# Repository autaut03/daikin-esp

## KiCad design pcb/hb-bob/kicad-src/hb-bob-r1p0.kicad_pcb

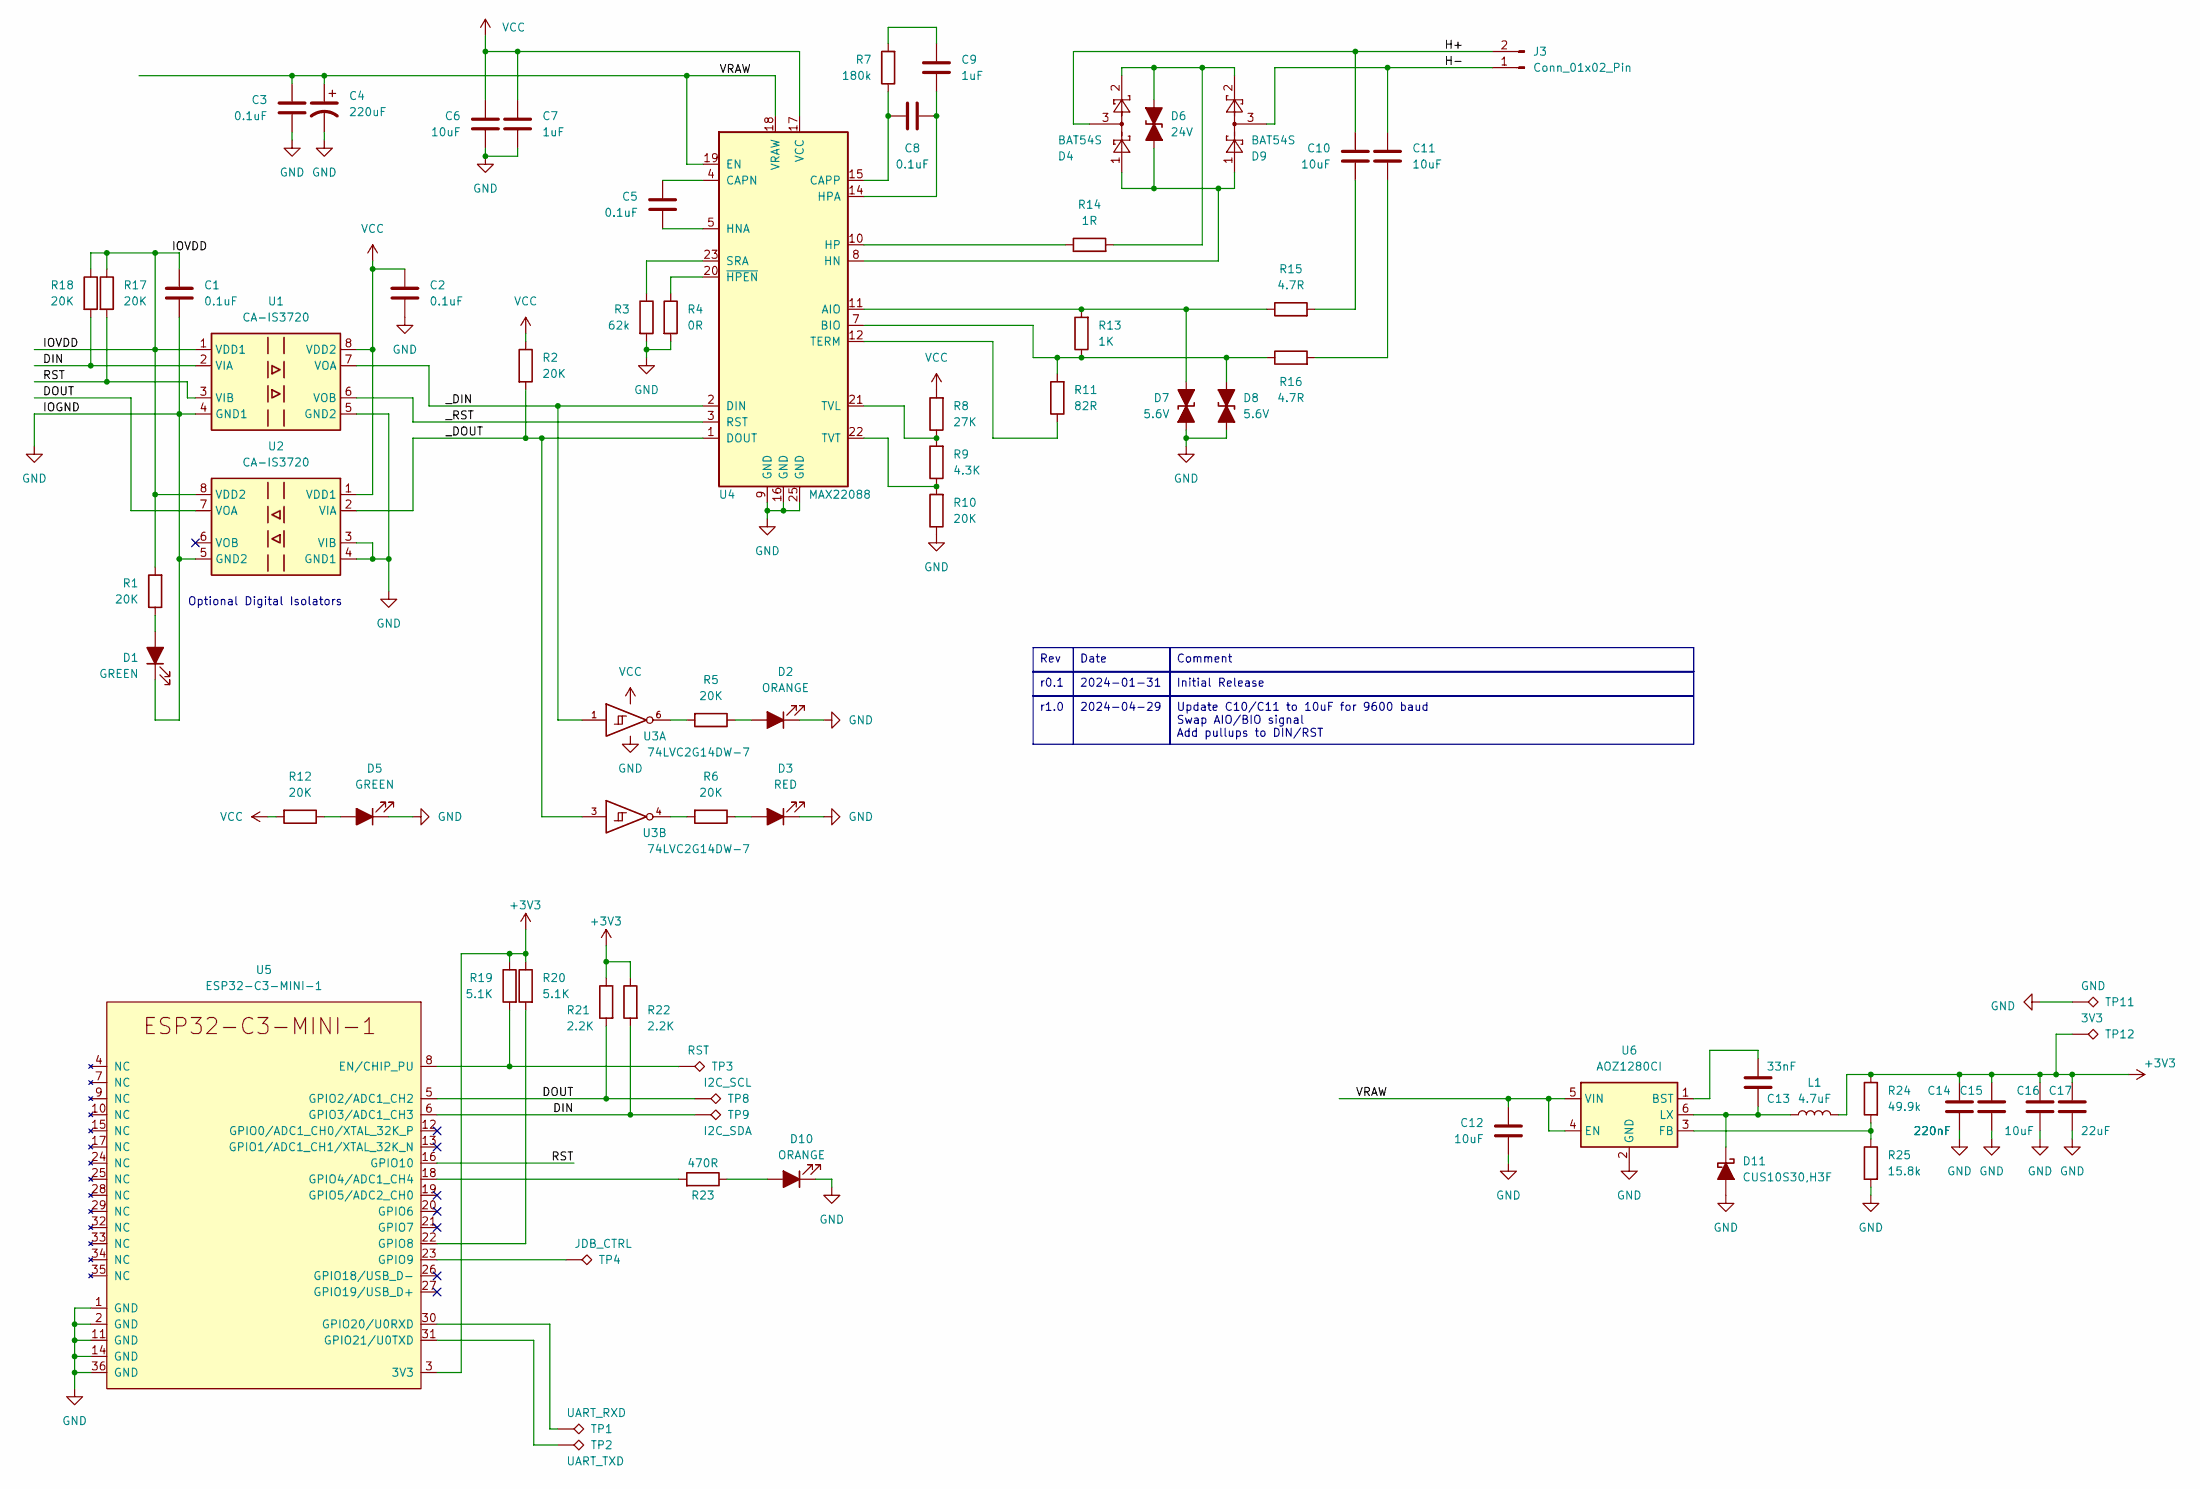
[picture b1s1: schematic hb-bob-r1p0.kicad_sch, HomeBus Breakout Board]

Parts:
C1, C2, C3, C5, C8: 0.1uF; C_0402_1005Metric; LCSC C1525
C4: 220uF; CP_EIA-7360-38_Kemet-E_Pad2.25x4.25mm_HandSolder; LCSC C2918361
C6, C10, C11: 10uF; C_0402_1005Metric; LCSC C15525
C7, C9: 1uF; C_0402_1005Metric; LCSC C52923
C12: 10uF; C_0603_1608Metric; LCSC C15850
C13: 33nF; C_0402_1005Metric; LCSC C106862
C14, C15: 220nF; C_0402_1005Metric; LCSC C16772
C16: 10uF; C_0603_1608Metric; LCSC C19702
C17: 22uF; C_0603_1608Metric; LCSC C59461
D1, D5: GREEN; LED_0402_1005Metric; LCSC C165980
D2: ORANGE; LED_0402_1005Metric; LCSC C165980
D3: RED; LED_0402_1005Metric; LCSC C165980
D4, D9: BAT54S; SOT-23; LCSC C916425
D6: 24V; D_SOD-123F; LCSC C908212
D7, D8: 5.6V; D_SOD-923; LCSC C151980
D10: ORANGE; LED_0402_1005Metric; LCSC C965791
D11: CUS10S30,H3F; D_SOD-523; LCSC C8523
J3: Conn_01x02_Pin; PinHeader_1x02_P2.54mm_Horizontal
L1: 4.7uF; L_0805_2012Metric; LCSC C63166
R1, R2, R5, R6, R10, R12, R17, R18: 20K; R_0402_1005Metric; LCSC C25765
R3: 62k; R_0402_1005Metric; LCSC C37825
R4: 0R; R_0402_1005Metric; LCSC C60485
R7: 180k; R_0402_1005Metric; LCSC C25760
R8: 27K; R_0402_1005Metric; LCSC C25771
R9: 4.3K; R_0402_1005Metric; LCSC C25899
R11: 82R; R_0402_1005Metric; LCSC C2909389
R13: 1K; R_0402_1005Metric; LCSC C11702
R14: 1R; R_0805_2012Metric; LCSC C131397
R15, R16: 4.7R; R_0603_1608Metric; LCSC C137705
R19, R20: 5.1K; R_0402_1005Metric; LCSC C25905
R21, R22: 2.2K; R_0402_1005Metric; LCSC C25879
R23: 470R; R_0402_1005Metric; LCSC C25117
R24: 49.9k; R_0402_1005Metric; LCSC C25897
R25: 15.8k; R_0402_1005Metric; LCSC C26956
TP1: UART_RXD; TestPoint_Pad_D1.0mm
TP2: UART_TXD; TestPoint_Pad_D1.0mm
TP3: RST; TestPoint_Pad_D1.0mm
TP4: JDB_CTRL; TestPoint_Pad_D1.0mm
TP8: I2C_SCL; TestPoint_Pad_D1.0mm
TP9: I2C_SDA; TestPoint_Pad_D1.0mm
TP11: GND; TestPoint_Pad_D1.0mm
TP12: 3V3; TestPoint_Pad_D1.0mm
U1, U2: CA-IS3720; SOIC-8_3.9x4.9mm_P1.27mm; LCSC C428882
U3: 74LVC2G14DW-7; SOT-363_SC-70-6; LCSC C362110
U4: MAX22088; QFN-24-1EP_4x4mm_P0.5mm_EP2.6x2.6mm; LCSC C5258925
U5: ESP32-C3-MINI-1; LCSC C2934569
U6: AOZ1280CI; SOT-23-6; LCSC C41240

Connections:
+3V3: C14.1, C15.1, C16.1, C17.1, L1.2, R19.1, R20.1, R21.1, R22.1, R24.1, TP12.1, U5.3 (3V3)
/DIN: R18.2, R22.2, TP9.1, U1.2 (VIA), U5.6 (GPIO3/ADC1_CH3)
/DOUT: R21.2, TP8.1, U2.7 (VOA), U5.5 (GPIO2/ADC1_CH2)
/H+: C10.2, D4.3, J3.2
/H-: C11.2, D9.3, J3.1
/IOVDD: C1.1, R1.2, R17.1, R18.1, U1.1 (VDD1), U2.8 (VDD2)
/RST: R17.2, U1.3 (VIB), U5.16 (GPIO10)
/VRAW: C3.1, C4.1, C12.1, U4.18 (VRAW), U4.19 (EN), U6.4 (EN), U6.5 (VIN)
/_DIN: U1.7 (VOA), U3.1, U4.2 (DIN)
/_DOUT: R2.2, U2.2 (VIA), U3.3, U4.1 (DOUT)
/_RST: U1.6 (VOB), U4.3 (RST)
GND: C1.2, C2.2, C3.2, C4.2, C6.2, C7.2, C12.2, C14.2, C15.2, C16.2, C17.2, D1.1 (K), D2.1 (K), D3.1 (K), D5.1 (K), D7.2 (A2), D8.2 (A2), D10.1 (K), D11.2 (A), R3.2, R4.2, R10.1, R25.2, TP11.1, U1.4 (GND1), U1.5 (GND2), U2.3 (VIB), U2.4 (GND1), U2.5 (GND2), U3.2 (GND), U4.9 (GND), U4.16 (GND), U4.25 (GND), U5.1 (GND), U5.2 (GND), U5.11 (GND), U5.14 (GND), U5.36 (GND), U5.37 (GND), U5.38 (GND), U5.39 (GND), U5.40 (GND), U5.41 (GND), U5.42 (GND), U5.43 (GND), U5.44 (GND), U5.45 (GND), U5.46 (GND), U5.47 (GND), U5.48 (GND), U5.49 (GND), U5.50 (GND), U5.51 (GND), U5.52 (GND), U5.53 (GND), U6.2 (GND)
unnamed: C9.1, R7.2
unnamed: C10.1, R15.2
unnamed: C11.1, R16.2
unnamed: D1.2 (A), R1.1
unnamed: D2.2 (A), R5.1
unnamed: D3.2 (A), R6.1
unnamed: D5.2 (A), R12.1
unnamed: D4.1, D6.1 (A1), D9.1, U4.8 (HN)
unnamed: D4.2, D6.2 (A2), D9.2, R14.2
unnamed: D7.1 (A1), R13.2, R15.1, U4.11 (AIO)
unnamed: D8.1 (A1), R11.2, R13.1, R16.1, U4.7 (BIO)
unnamed: D10.2 (A), R23.1
unnamed: C13.1, D11.1 (K), L1.1, U6.6 (LX)
unnamed: R5.2, U3.6
unnamed: R6.2, U3.4
unnamed: C5.1, U4.4 (CAPN)
unnamed: C8.2, R7.1, U4.15 (CAPP)
unnamed: C5.2, U4.5 (HNA)
unnamed: R14.1, U4.10 (HP)
unnamed: C8.1, C9.2, U4.14 (HPA)
unnamed: R3.1, U4.23 (SRA)
unnamed: R11.1, U4.12 (TERM)
unnamed: R8.1, R9.2, U4.21 (TVL)
unnamed: R9.1, R10.2, U4.22 (TVT)
unnamed: R4.1, U4.20 (~HPEN)
unnamed: R19.2, TP3.1, U5.8 (EN/CHIP_PU)
unnamed: R23.2, U5.18 (GPIO4/ADC1_CH4)
unnamed: R20.2, U5.22 (GPIO8)
unnamed: TP4.1, U5.23 (GPIO9)
unnamed: TP1.1, U5.30 (GPIO20/U0RXD)
unnamed: TP2.1, U5.31 (GPIO21/U0TXD)
unnamed: C13.2, U6.1 (BST)
unnamed: R24.2, R25.1, U6.3 (FB)
VCC: C2.1, C6.1, C7.1, R2.1, R8.2, R12.2, U1.8 (VDD2), U2.1 (VDD1), U3.5 (VCC), U4.17 (VCC)

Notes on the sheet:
Optional Digital Isolators
r0.1
2024-04-29
Initial Release
Update C10/C11 to 10uF for 9600 baud Swap AIO/BIO signal Add pullups to DIN/RST
Comment
Rev
2024-01-31
Date
r1.0

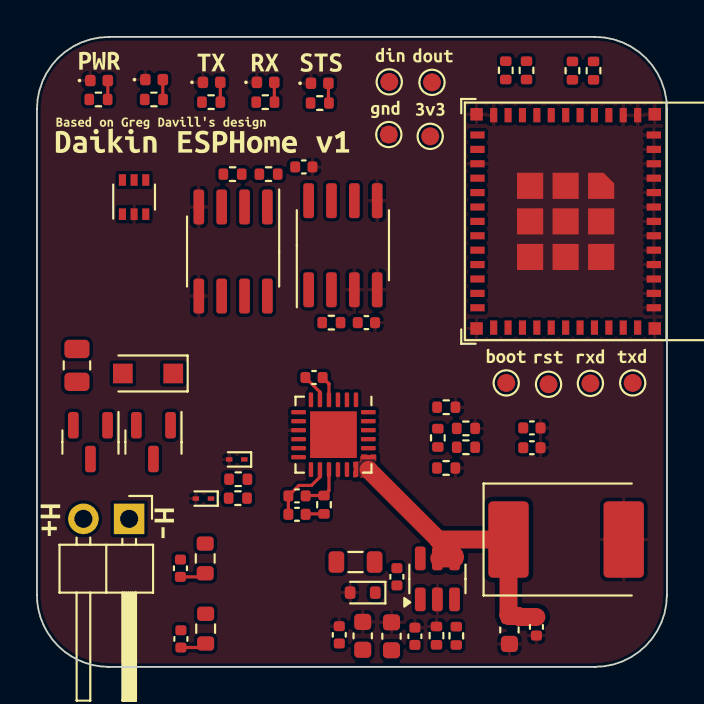
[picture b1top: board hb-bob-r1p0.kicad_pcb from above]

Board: 2 copper layers, 35.0 x 35.0 mm, 85 parts (0 on the bottom side), 46 nets.

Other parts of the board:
kibuzzard-65B6C60D: G***; kibuzzard-65B6C60D
kibuzzard-65B6C61A: G***; kibuzzard-65B6C61A
kibuzzard-65B629C5: G***; kibuzzard-65B629C5
kibuzzard-65B629E6: G***; kibuzzard-65B629E6
kibuzzard-65B629EE: G***; kibuzzard-65B629EE
kibuzzard-68B31F11: G***; kibuzzard-68B31F11
kibuzzard-68B31F54: G***; kibuzzard-68B31F54
kibuzzard-68B31FE4: G***; kibuzzard-68B31FE4
kibuzzard-68B326CE: G***; kibuzzard-68B326CE
kibuzzard-68B326E4: G***; kibuzzard-68B326E4
kibuzzard-68B326FE: G***; kibuzzard-68B326FE
kibuzzard-68B3271E: G***; kibuzzard-68B3271E
kibuzzard-68B3273B: G***; kibuzzard-68B3273B
kibuzzard-68B32675: G***; kibuzzard-68B32675
kibuzzard-68B32731: G***; kibuzzard-68B32731
kibuzzard-68B32786: G***; kibuzzard-68B32786

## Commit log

2025-08-31 wip: combined into one pcb
